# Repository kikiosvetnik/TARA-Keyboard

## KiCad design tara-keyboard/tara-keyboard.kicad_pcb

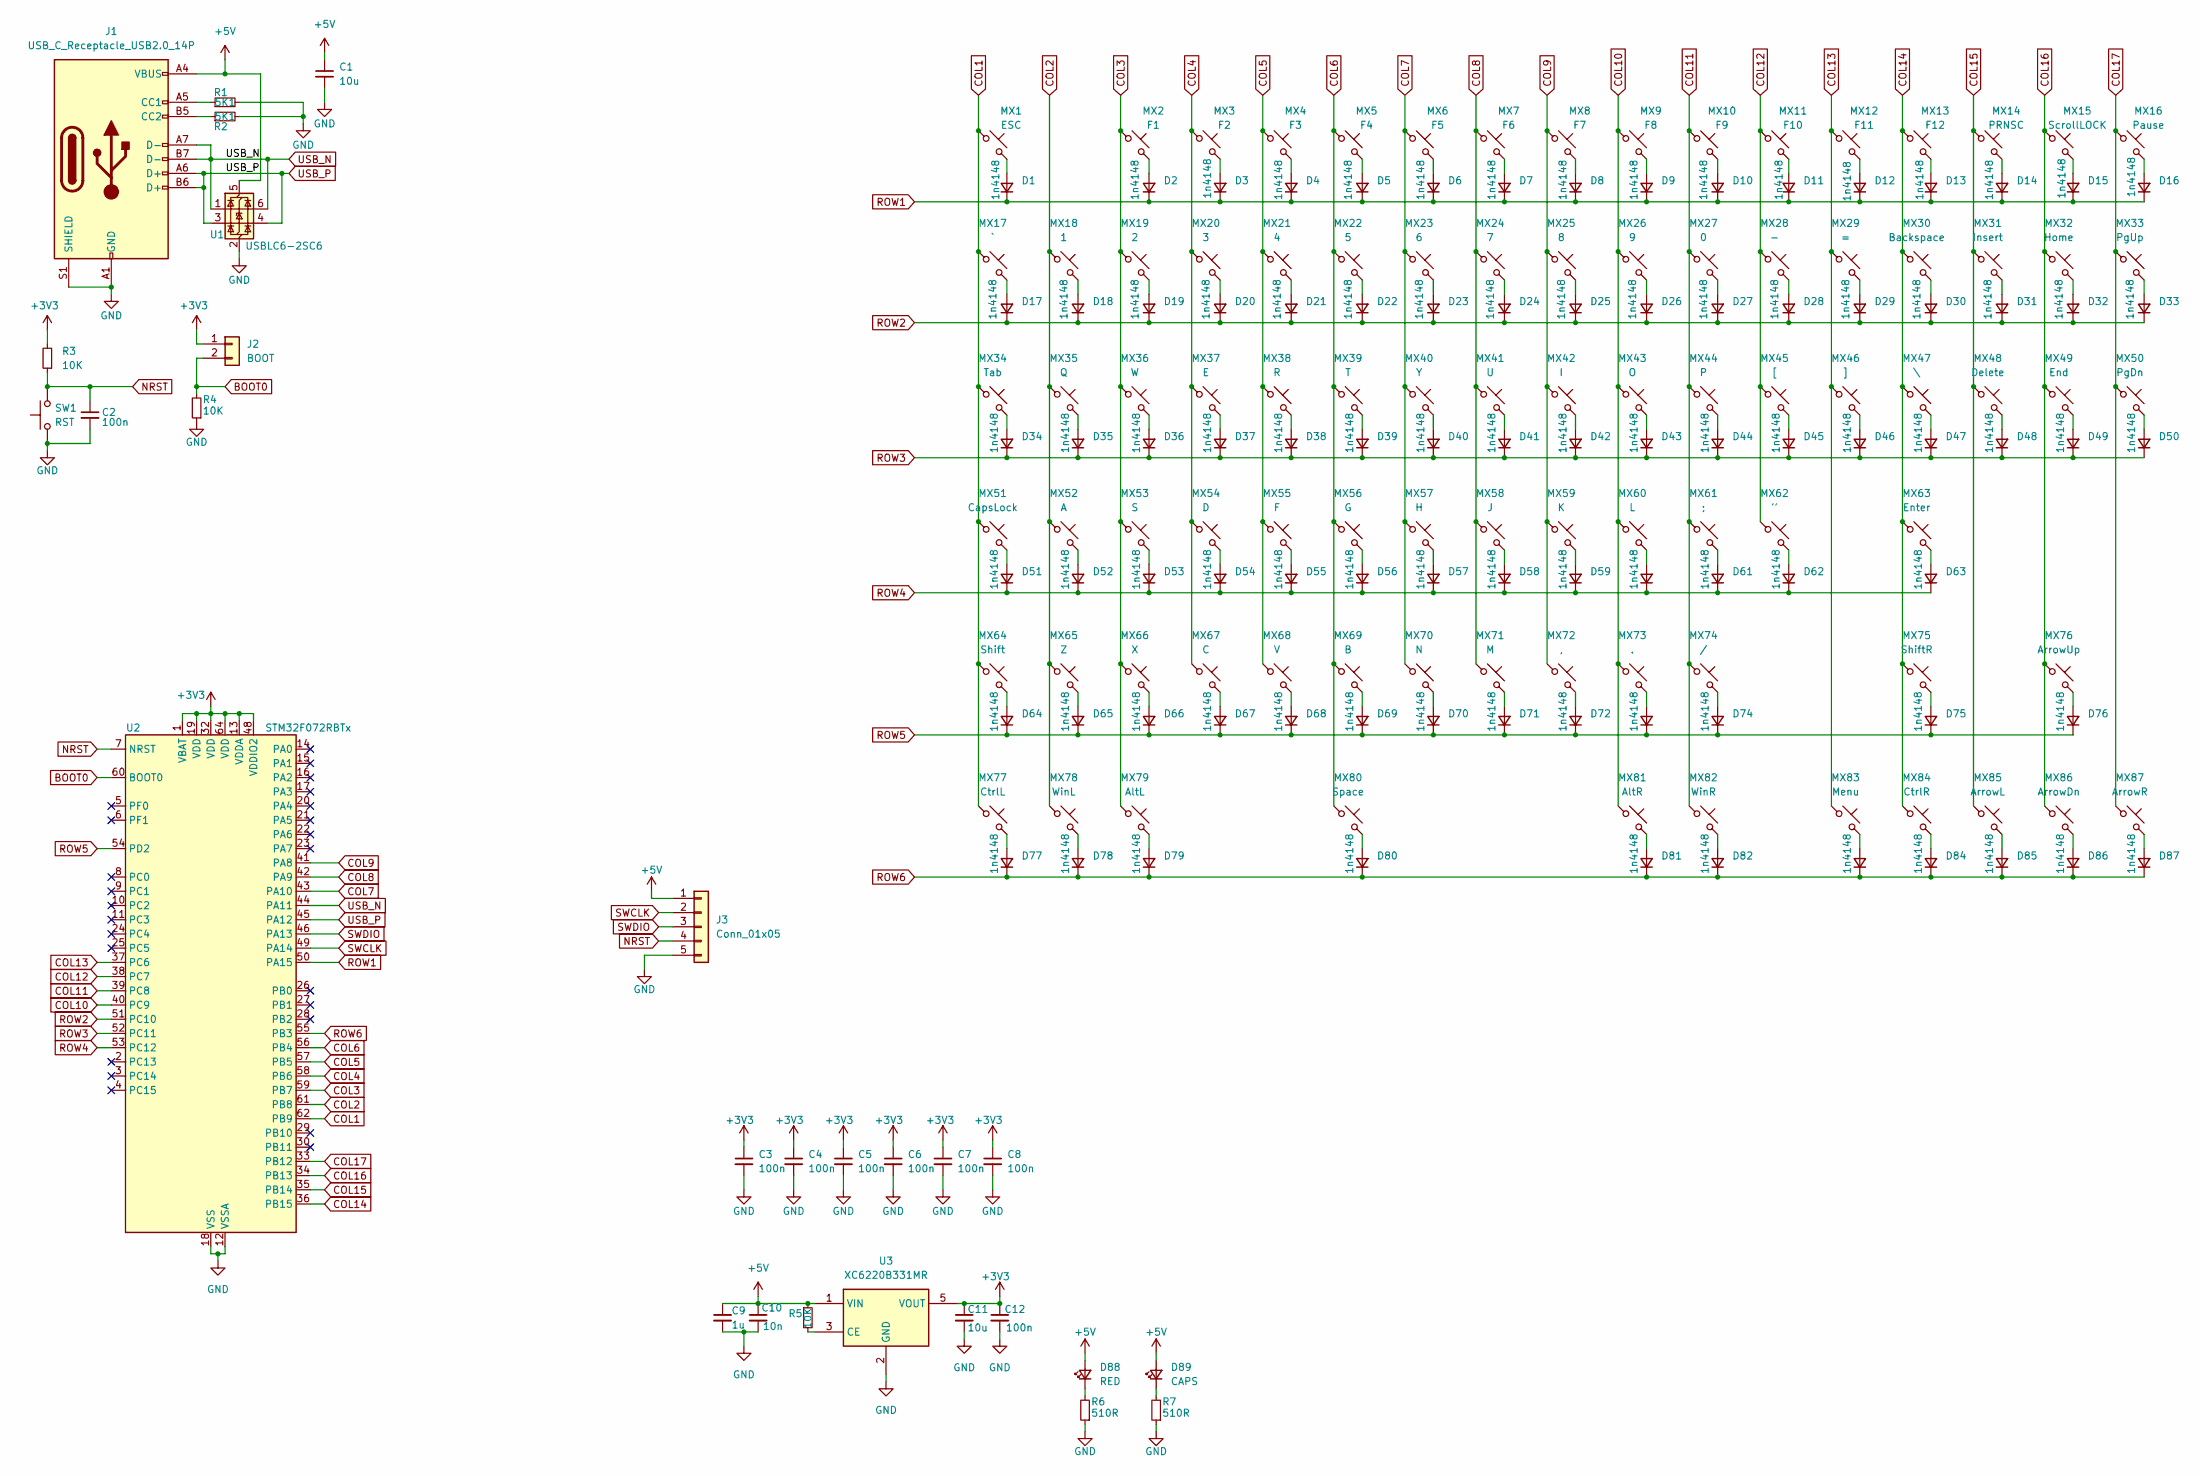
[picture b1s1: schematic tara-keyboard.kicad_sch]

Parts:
C1: 10u; C_1206_3216Metric
C2, C3, C4, C5, C6, C7, C8: 100n; C_0402_1005Metric
C9: 1u; C_0603_1608Metric
C10: 10n; C_0603_1608Metric
C11: 10u; C_0603_1608Metric
C12: 100n; C_0603_1608Metric
D1, D2, D3, D4, D5, D6, D7, D8, D9, D10, D11, D12, D13, D14, D15, D16, D17, D18, D19, D20, D21, D22, D23, D24, D25, D26, D27, D28, D29, D30, D31, D32, D33, D34, D35, D36, D37, D38, D39, D40, D41, D42, D43, D44, D45, D46, D47, D48, D49, D50, D51, D52, D53, D54, D55, D56, D57, D58, D59, D60, D61, D62, D63, D64, D65, D66, D67, D68, D69, D70, D71, D72, D73, D74, D75, D76, D77, D78, D79, D80, D81, D82, D83, D84, D85, D86, D87: 1n4148; D_SOD-123
D88: RED; LED_0603_1608Metric
D89: CAPS; LED_0603_1608Metric
J1: USB_C_Receptacle_USB2.0_14P; USB_C_Receptacle_GCT_USB4105-xx-A_16P_TopMnt_Horizontal
J2: BOOT; PinHeader_1x02_P2.54mm_Vertical
J3: Conn_01x05; PinHeader_1x05_P2.54mm_Vertical
MX1: ESC; SW_Cherry_MX_PCB_1.00u
MX2: F1; SW_Cherry_MX_PCB_1.00u
MX3: F2; SW_Cherry_MX_PCB_1.00u
MX4: F3; SW_Cherry_MX_PCB_1.00u
MX5: F4; SW_Cherry_MX_PCB_1.00u
MX6: F5; SW_Cherry_MX_PCB_1.00u
MX7: F6; SW_Cherry_MX_PCB_1.00u
MX8: F7; SW_Cherry_MX_PCB_1.00u
MX9: F8; SW_Cherry_MX_PCB_1.00u
MX10: F9; SW_Cherry_MX_PCB_1.00u
MX11: F10; SW_Cherry_MX_PCB_1.00u
MX12: F11; SW_Cherry_MX_PCB_1.00u
MX13: F12; SW_Cherry_MX_PCB_1.00u
MX14: PRNSC; SW_Cherry_MX_PCB_1.00u
MX15: ScrollLOCK; SW_Cherry_MX_PCB_1.00u
MX16: Pause; SW_Cherry_MX_PCB_1.00u
MX17: `; SW_Cherry_MX_PCB_1.00u
MX18: 1; SW_Cherry_MX_PCB_1.00u
MX19: 2; SW_Cherry_MX_PCB_1.00u
MX20: 3; SW_Cherry_MX_PCB_1.00u
MX21: 4; SW_Cherry_MX_PCB_1.00u
MX22: 5; SW_Cherry_MX_PCB_1.00u
MX23: 6; SW_Cherry_MX_PCB_1.00u
MX24: 7; SW_Cherry_MX_PCB_1.00u
MX25: 8; SW_Cherry_MX_PCB_1.00u
MX26: 9; SW_Cherry_MX_PCB_1.00u
MX27: 0; SW_Cherry_MX_PCB_1.00u
MX28: -; SW_Cherry_MX_PCB_1.00u
MX29: =; SW_Cherry_MX_PCB_1.00u
MX30: Backspace; SW_Cherry_MX_PCB_2.00u
MX31: Insert; SW_Cherry_MX_PCB_1.00u
MX32: Home; SW_Cherry_MX_PCB_1.00u
MX33: PgUp; SW_Cherry_MX_PCB_1.00u
MX34: Tab; SW_Cherry_MX_PCB_1.00u
MX35: Q; SW_Cherry_MX_PCB_1.00u
MX36: W; SW_Cherry_MX_PCB_1.00u
MX37: E; SW_Cherry_MX_PCB_1.00u
MX38: R; SW_Cherry_MX_PCB_1.00u
MX39: T; SW_Cherry_MX_PCB_1.00u
MX40: Y; SW_Cherry_MX_PCB_1.00u
MX41: U; SW_Cherry_MX_PCB_1.00u
MX42: I; SW_Cherry_MX_PCB_1.00u
MX43: O; SW_Cherry_MX_PCB_1.00u
MX44: P; SW_Cherry_MX_PCB_1.00u
MX45: [; SW_Cherry_MX_PCB_1.00u
MX46: ]; SW_Cherry_MX_PCB_1.00u
MX47: \; SW_Cherry_MX_PCB_1.50u
MX48: Delete; SW_Cherry_MX_PCB_1.00u
MX49: End; SW_Cherry_MX_PCB_1.00u
MX50: PgDn; SW_Cherry_MX_PCB_1.00u
MX51: CapsLock; SW_Cherry_MX_PCB_1.75u
MX52: A; SW_Cherry_MX_PCB_1.00u
MX53: S; SW_Cherry_MX_PCB_1.00u
MX54: D; SW_Cherry_MX_PCB_1.00u
MX55: F; SW_Cherry_MX_PCB_1.00u
MX56: G; SW_Cherry_MX_PCB_1.00u
MX57: H; SW_Cherry_MX_PCB_1.00u
MX58: J; SW_Cherry_MX_PCB_1.00u
MX59: K; SW_Cherry_MX_PCB_1.00u
MX60: L; SW_Cherry_MX_PCB_1.00u
MX61: ;; SW_Cherry_MX_PCB_1.00u
MX62: ''; SW_Cherry_MX_PCB_1.00u
MX63: Enter; SW_Cherry_MX_PCB_2.25u
MX64: Shift; SW_Cherry_MX_PCB_2.25u
MX65: Z; SW_Cherry_MX_PCB_1.00u
MX66: X; SW_Cherry_MX_PCB_1.00u
MX67: C; SW_Cherry_MX_PCB_1.00u
MX68: V; SW_Cherry_MX_PCB_1.00u
MX69: B; SW_Cherry_MX_PCB_1.00u
MX70: N; SW_Cherry_MX_PCB_1.00u
MX71: M; SW_Cherry_MX_PCB_1.00u
MX72: ,; SW_Cherry_MX_PCB_1.00u
MX73: .; SW_Cherry_MX_PCB_1.00u
MX74: /; SW_Cherry_MX_PCB_1.00u
MX75: ShiftR; SW_Cherry_MX_PCB_2.75u
MX76: ArrowUp; SW_Cherry_MX_PCB_1.00u
MX77: CtrlL; SW_Cherry_MX_PCB_1.25u
MX78: WinL; SW_Cherry_MX_PCB_1.25u
MX79: AltL; SW_Cherry_MX_PCB_1.25u
MX80: Space; SW_Cherry_MX_PCB_6.25u
MX81: AltR; SW_Cherry_MX_PCB_1.25u
MX82: WinR; SW_Cherry_MX_PCB_1.25u
MX83: Menu; SW_Cherry_MX_PCB_1.25u
MX84: CtrlR; SW_Cherry_MX_PCB_1.25u
MX85: ArrowL; SW_Cherry_MX_PCB_1.00u
MX86: ArrowDn; SW_Cherry_MX_PCB_1.00u
MX87: ArrowR; SW_Cherry_MX_PCB_1.00u
R1, R2: 5K1; R_0402_1005Metric
R3, R4, R5: 10K; R_0402_1005Metric
R6, R7: 510R; R_0402_1005Metric
SW1: RST; SW_SPST_B3U-1000P
U1: USBLC6-2SC6; SOT-23-6
U2: STM32F072RBTx; LQFP-64_10x10mm_P0.5mm
U3: XC6220B331MR; SOT-23-5

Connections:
+3V3: C3.1, C4.1, C5.1, C6.1, C7.1, C8.1, C11.1, C12.1, J2.1, R3.2, U2.1 (VBAT), U2.13 (VDDA), U2.19 (VDD), U2.32 (VDD), U2.48 (VDDIO2), U2.64 (VDD), U3.5 (VOUT)
+5V: C1.1, C9.1, C10.1, D88.2 (A), D89.2 (A), J1.A4 (VBUS), J1.A9 (VBUS), J1.B4 (VBUS), J1.B9 (VBUS), J3.1, R5.1, U1.5 (VBUS), U3.1 (VIN)
BOOT0: J2.2, R4.2, U2.60 (BOOT0)
COL1: MX1.1, MX17.1, MX34.1, MX51.1, MX64.1, MX77.1, U2.62 (PB9)
COL2: MX18.1, MX35.1, MX52.1, MX65.1, MX78.1, U2.61 (PB8)
COL3: MX2.1, MX19.1, MX36.1, MX53.1, MX66.1, MX79.1, U2.59 (PB7)
COL4: MX3.1, MX20.1, MX37.1, MX54.1, MX67.1, U2.58 (PB6)
COL5: MX4.1, MX21.1, MX38.1, MX55.1, MX68.1, U2.57 (PB5)
COL6: MX5.1, MX22.1, MX39.1, MX56.1, MX69.1, MX80.1, U2.56 (PB4)
COL7: MX6.1, MX23.1, MX40.1, MX57.1, MX70.1, U2.43 (PA10)
COL8: MX7.1, MX24.1, MX41.1, MX58.1, MX71.1, U2.42 (PA9)
COL9: MX8.1, MX25.1, MX42.1, MX59.1, MX72.1, U2.41 (PA8)
COL10: MX9.1, MX26.1, MX43.1, MX60.1, MX73.1, MX81.1, U2.40 (PC9)
COL11: MX10.1, MX27.1, MX44.1, MX61.1, MX74.1, MX82.1, U2.39 (PC8)
COL12: MX11.1, MX28.1, MX45.1, MX62.1, U2.38 (PC7)
COL13: MX12.1, MX29.1, MX46.1, MX83.1, U2.37 (PC6)
COL14: MX13.1, MX30.1, MX47.1, MX63.1, MX75.1, MX84.1, U2.36 (PB15)
COL15: MX14.1, MX31.1, MX48.1, MX85.1, U2.35 (PB14)
COL16: MX15.1, MX32.1, MX49.1, MX76.1, MX86.1, U2.34 (PB13)
COL17: MX16.1, MX33.1, MX50.1, MX87.1, U2.33 (PB12)
GND: C1.2, C2.2, C3.2, C4.2, C5.2, C6.2, C7.2, C8.2, C9.2, C10.2, C11.2, C12.2, J1.A1 (GND), J1.A12 (GND), J1.B1 (GND), J1.B12 (GND), J1.S1 (SHIELD), J3.5, R1.2, R2.2, R4.1, R6.1, R7.1, SW1.1, U1.2 (GND), U2.12 (VSSA), U2.18 (VSS), U2.31 (VSS), U2.47 (VSS), U2.63 (VSS), U3.2 (GND)
NRST: C2.1, J3.4, R3.1, SW1.2, U2.7 (NRST)
unnamed: D1.2 (A), MX1.2
unnamed: D2.2 (A), MX2.2
unnamed: D3.2 (A), MX3.2
unnamed: D4.2 (A), MX4.2
unnamed: D5.2 (A), MX5.2
unnamed: D6.2 (A), MX6.2
unnamed: D7.2 (A), MX7.2
unnamed: D8.2 (A), MX8.2
unnamed: D9.2 (A), MX9.2
unnamed: D10.2 (A), MX10.2
unnamed: D11.2 (A), MX11.2
unnamed: D12.2 (A), MX12.2
unnamed: D13.2 (A), MX13.2
unnamed: D14.2 (A), MX14.2
unnamed: D15.2 (A), MX15.2
unnamed: D16.2 (A), MX16.2
unnamed: D17.2 (A), MX17.2
unnamed: D18.2 (A), MX18.2
unnamed: D19.2 (A), MX19.2
unnamed: D20.2 (A), MX20.2
unnamed: D21.2 (A), MX21.2
unnamed: D22.2 (A), MX22.2
unnamed: D23.2 (A), MX23.2
unnamed: D24.2 (A), MX24.2
unnamed: D25.2 (A), MX25.2
unnamed: D26.2 (A), MX26.2
unnamed: D27.2 (A), MX27.2
unnamed: D28.2 (A), MX28.2
unnamed: D29.2 (A), MX29.2
unnamed: D30.2 (A), MX30.2
unnamed: D31.2 (A), MX31.2
unnamed: D32.2 (A), MX32.2
unnamed: D33.2 (A), MX33.2
unnamed: D34.2 (A), MX34.2
unnamed: D35.2 (A), MX35.2
unnamed: D36.2 (A), MX36.2
unnamed: D37.2 (A), MX37.2
unnamed: D38.2 (A), MX38.2
unnamed: D39.2 (A), MX39.2
unnamed: D40.2 (A), MX40.2
unnamed: D41.2 (A), MX41.2
unnamed: D42.2 (A), MX42.2
unnamed: D43.2 (A), MX43.2
unnamed: D44.2 (A), MX44.2
unnamed: D45.2 (A), MX45.2
unnamed: D46.2 (A), MX46.2
unnamed: D47.2 (A), MX47.2
unnamed: D48.2 (A), MX48.2
unnamed: D49.2 (A), MX49.2
unnamed: D50.2 (A), MX50.2
unnamed: D51.2 (A), MX51.2
unnamed: D52.2 (A), MX52.2
unnamed: D53.2 (A), MX53.2
unnamed: D54.2 (A), MX54.2
unnamed: D55.2 (A), MX55.2
unnamed: D56.2 (A), MX56.2
unnamed: D57.2 (A), MX57.2
unnamed: D58.2 (A), MX58.2
unnamed: D59.2 (A), MX59.2
unnamed: D60.2 (A), MX60.2
unnamed: D61.2 (A), MX61.2
unnamed: D62.2 (A), MX62.2
unnamed: D63.2 (A), MX63.2
unnamed: D64.2 (A), MX64.2
unnamed: D65.2 (A), MX65.2
unnamed: D66.2 (A), MX66.2
unnamed: D67.2 (A), MX67.2
unnamed: D68.2 (A), MX68.2
unnamed: D69.2 (A), MX69.2
unnamed: D70.2 (A), MX70.2
unnamed: D71.2 (A), MX71.2
unnamed: D72.2 (A), MX72.2
unnamed: D73.2 (A), MX73.2
unnamed: D74.2 (A), MX74.2
unnamed: D75.2 (A), MX75.2
unnamed: D76.2 (A), MX76.2
unnamed: D77.2 (A), MX77.2
unnamed: D78.2 (A), MX78.2
unnamed: D79.2 (A), MX79.2
unnamed: D80.2 (A), MX80.2
unnamed: D81.2 (A), MX81.2
unnamed: D82.2 (A), MX82.2
unnamed: D83.2 (A), MX83.2
unnamed: D84.2 (A), MX84.2
unnamed: D85.2 (A), MX85.2
unnamed: D86.2 (A), MX86.2
unnamed: D87.2 (A), MX87.2
unnamed: D88.1 (K), R6.2
unnamed: D89.1 (K), R7.2
unnamed: J1.A5 (CC1), R1.1
unnamed: J1.B5 (CC2), R2.1
unnamed: R5.2, U3.3 (CE)
ROW1: D1.1 (K), D2.1 (K), D3.1 (K), D4.1 (K), D5.1 (K), D6.1 (K), D7.1 (K), D8.1 (K), D9.1 (K), D10.1 (K), D11.1 (K), D12.1 (K), D13.1 (K), D14.1 (K), D15.1 (K), D16.1 (K), U2.50 (PA15)
ROW2: D17.1 (K), D18.1 (K), D19.1 (K), D20.1 (K), D21.1 (K), D22.1 (K), D23.1 (K), D24.1 (K), D25.1 (K), D26.1 (K), D27.1 (K), D28.1 (K), D29.1 (K), D30.1 (K), D31.1 (K), D32.1 (K), D33.1 (K), U2.51 (PC10)
ROW3: D34.1 (K), D35.1 (K), D36.1 (K), D37.1 (K), D38.1 (K), D39.1 (K), D40.1 (K), D41.1 (K), D42.1 (K), D43.1 (K), D44.1 (K), D45.1 (K), D46.1 (K), D47.1 (K), D48.1 (K), D49.1 (K), D50.1 (K), U2.52 (PC11)
ROW4: D51.1 (K), D52.1 (K), D53.1 (K), D54.1 (K), D55.1 (K), D56.1 (K), D57.1 (K), D58.1 (K), D59.1 (K), D60.1 (K), D61.1 (K), D62.1 (K), D63.1 (K), U2.53 (PC12)
ROW5: D64.1 (K), D65.1 (K), D66.1 (K), D67.1 (K), D68.1 (K), D69.1 (K), D70.1 (K), D71.1 (K), D72.1 (K), D73.1 (K), D74.1 (K), D75.1 (K), D76.1 (K), U2.54 (PD2)
ROW6: D77.1 (K), D78.1 (K), D79.1 (K), D80.1 (K), D81.1 (K), D82.1 (K), D83.1 (K), D84.1 (K), D85.1 (K), D86.1 (K), D87.1 (K), U2.55 (PB3)
SWCLK: J3.2, U2.49 (PA14)
SWDIO: J3.3, U2.46 (PA13)
USB_N: J1.A7 (D-), J1.B7 (D-), U1.1 (I/O1), U1.6 (I/O1), U2.44 (PA11)
USB_P: J1.A6 (D+), J1.B6 (D+), U1.3 (I/O2), U1.4 (I/O2), U2.45 (PA12)

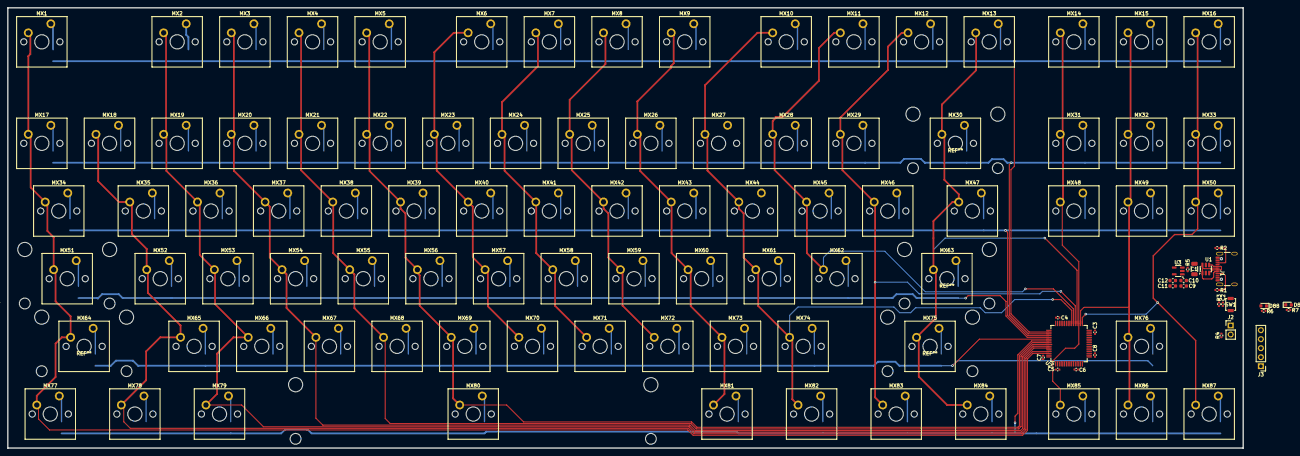
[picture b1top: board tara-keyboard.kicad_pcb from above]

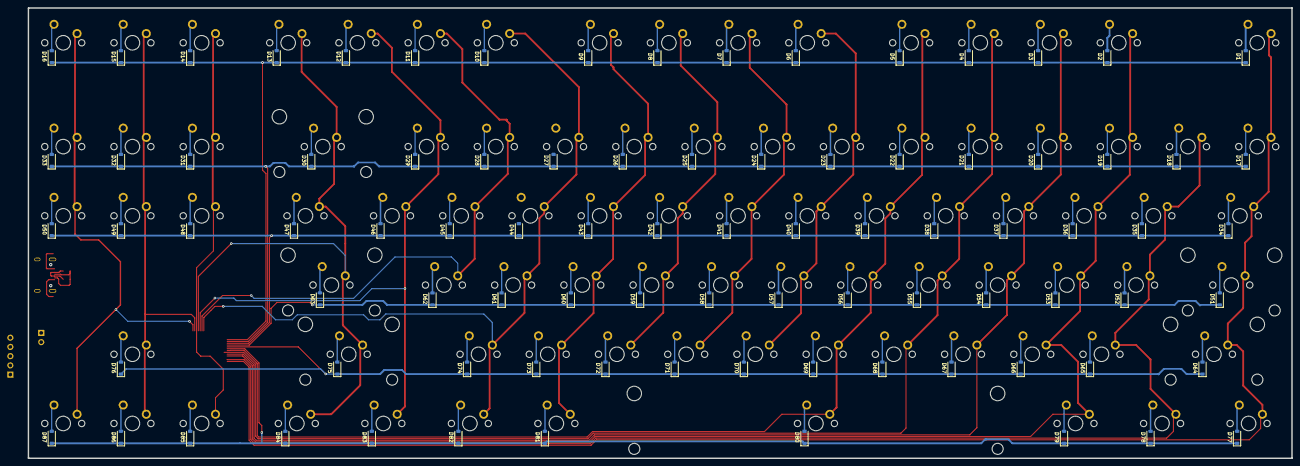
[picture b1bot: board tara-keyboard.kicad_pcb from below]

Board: 4 copper layers, 347.8 x 123.9 mm, 202 parts (87 on the bottom side), 124 nets.

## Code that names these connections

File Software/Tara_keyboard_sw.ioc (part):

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Mcu.Name=STM32F072R(8-B)Tx
Mcu.Package=LQFP64
Mcu.UserName=STM32F072RBTx
PA11.Mode=Device
PA11.Signal=USB_DM
PA12.Mode=Device
PA12.Signal=USB_DP
PA13.Mode=Serial_Wire
PA13.Signal=SYS_SWDIO
PA14.Mode=Serial_Wire
PA14.Signal=SYS_SWCLK
board=custom

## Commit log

2025-01-01 Inital Commit.
2025-01-01 Added Inital Files for versioning of project.
2025-01-02 :construction: work in progress.
2025-01-03 :rocket: Added finished PCB and generated Step Model.
